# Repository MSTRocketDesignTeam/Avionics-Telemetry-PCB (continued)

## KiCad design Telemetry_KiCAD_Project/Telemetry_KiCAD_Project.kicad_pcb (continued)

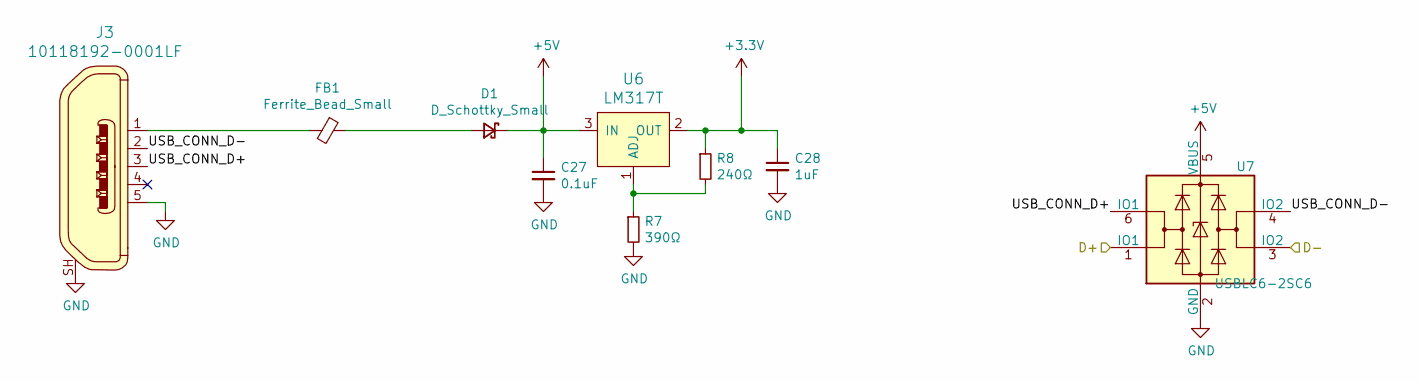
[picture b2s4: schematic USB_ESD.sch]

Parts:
C27: 0.1uF; C_0603_1608Metric
C28: 1uF; C_0603_1608Metric
D1: D_Schottky_Small; D_0201_0603Metric
FB1: Ferrite_Bead_Small; C_0603_1608Metric
J3: 10118192-0001LF; USB_Micro-B_Molex_47346-0001; MPN 10118192-0001LF; Digi-Key_PN 609-4613-1-ND
R7: 390Ω; 0603
R8: 240Ω; 0603
U6: LM317T; TO-252-3_TabPin2; MPN LM317T; Digi-Key_PN 497-1575-5-ND
U7: USBLC6-2SC6; SOT-23-6

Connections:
+3V3: C28.1, R8.1, U6.2 (OUT); also elsewhere on the board
+5V: C27.1, D1.1 (K), U6.3 (IN), U7.5 (VBUS); also elsewhere on the board
/USB Connector and ESD/D+: U7.1 (IO1); also elsewhere on the board
/USB Connector and ESD/D-: U7.3 (IO2); also elsewhere on the board
/USB Connector and ESD/USB_CONN_D+: J3.3, U7.6 (IO1)
/USB Connector and ESD/USB_CONN_D-: J3.2, U7.4 (IO2)
GND: C27.2, C28.2, J3.5, J3.SH, R7.2, U7.2 (GND); also elsewhere on the board
unnamed: D1.2 (A), FB1.1
unnamed: FB1.2, J3.1
unnamed: R7.1, R8.2, U6.1 (ADJ)

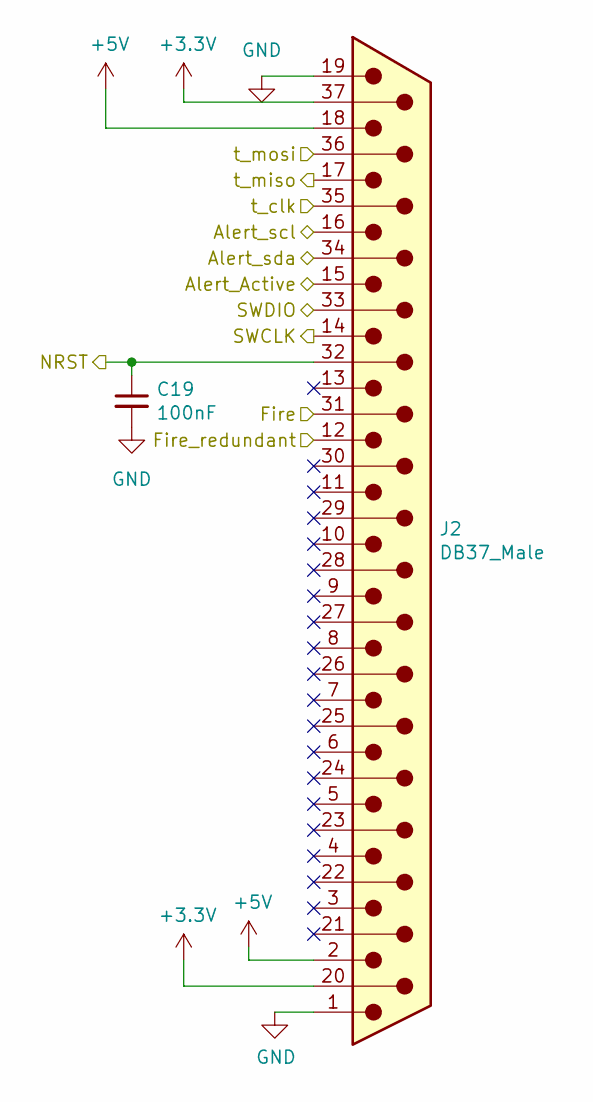
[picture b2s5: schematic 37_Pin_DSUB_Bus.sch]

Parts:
C19: 100nF; C_0603_1608Metric
J2: DB37_Male; DSUB-37_Male_Horizontal_P2.77x2.84mm_EdgePinOffset9.90mm_Ho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

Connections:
+3V3: J2.20, J2.37; also elsewhere on the board
+5V: J2.2, J2.18; also elsewhere on the board
/37_Pin_DSUB_Bus/Alert_Active: J2.15; also elsewhere on the board
/37_Pin_DSUB_Bus/Alert_scl: J2.16; also elsewhere on the board
/37_Pin_DSUB_Bus/Alert_sda: J2.34; also elsewhere on the board
/37_Pin_DSUB_Bus/NRST: C19.1, J2.32; also elsewhere on the board
/MCU_L562VE/ABORT_1: J2.31; also elsewhere on the board
/MCU_L562VE/ABORT_2: J2.12; also elsewhere on the board
/MCU_L562VE/DEBUG_SWCLK: J2.14; also elsewhere on the board
/MCU_L562VE/DEBUG_SWDIO: J2.33; also elsewhere on the board
/MCU_L562VE/SPI1_MISO: J2.17; also elsewhere on the board
/MCU_L562VE/SPI1_MOSI: J2.36; also elsewhere on the board
/MCU_L562VE/SPI1_SCK: J2.35; also elsewhere on the board
GND: C19.2, J2.1, J2.19; also elsewhere on the board

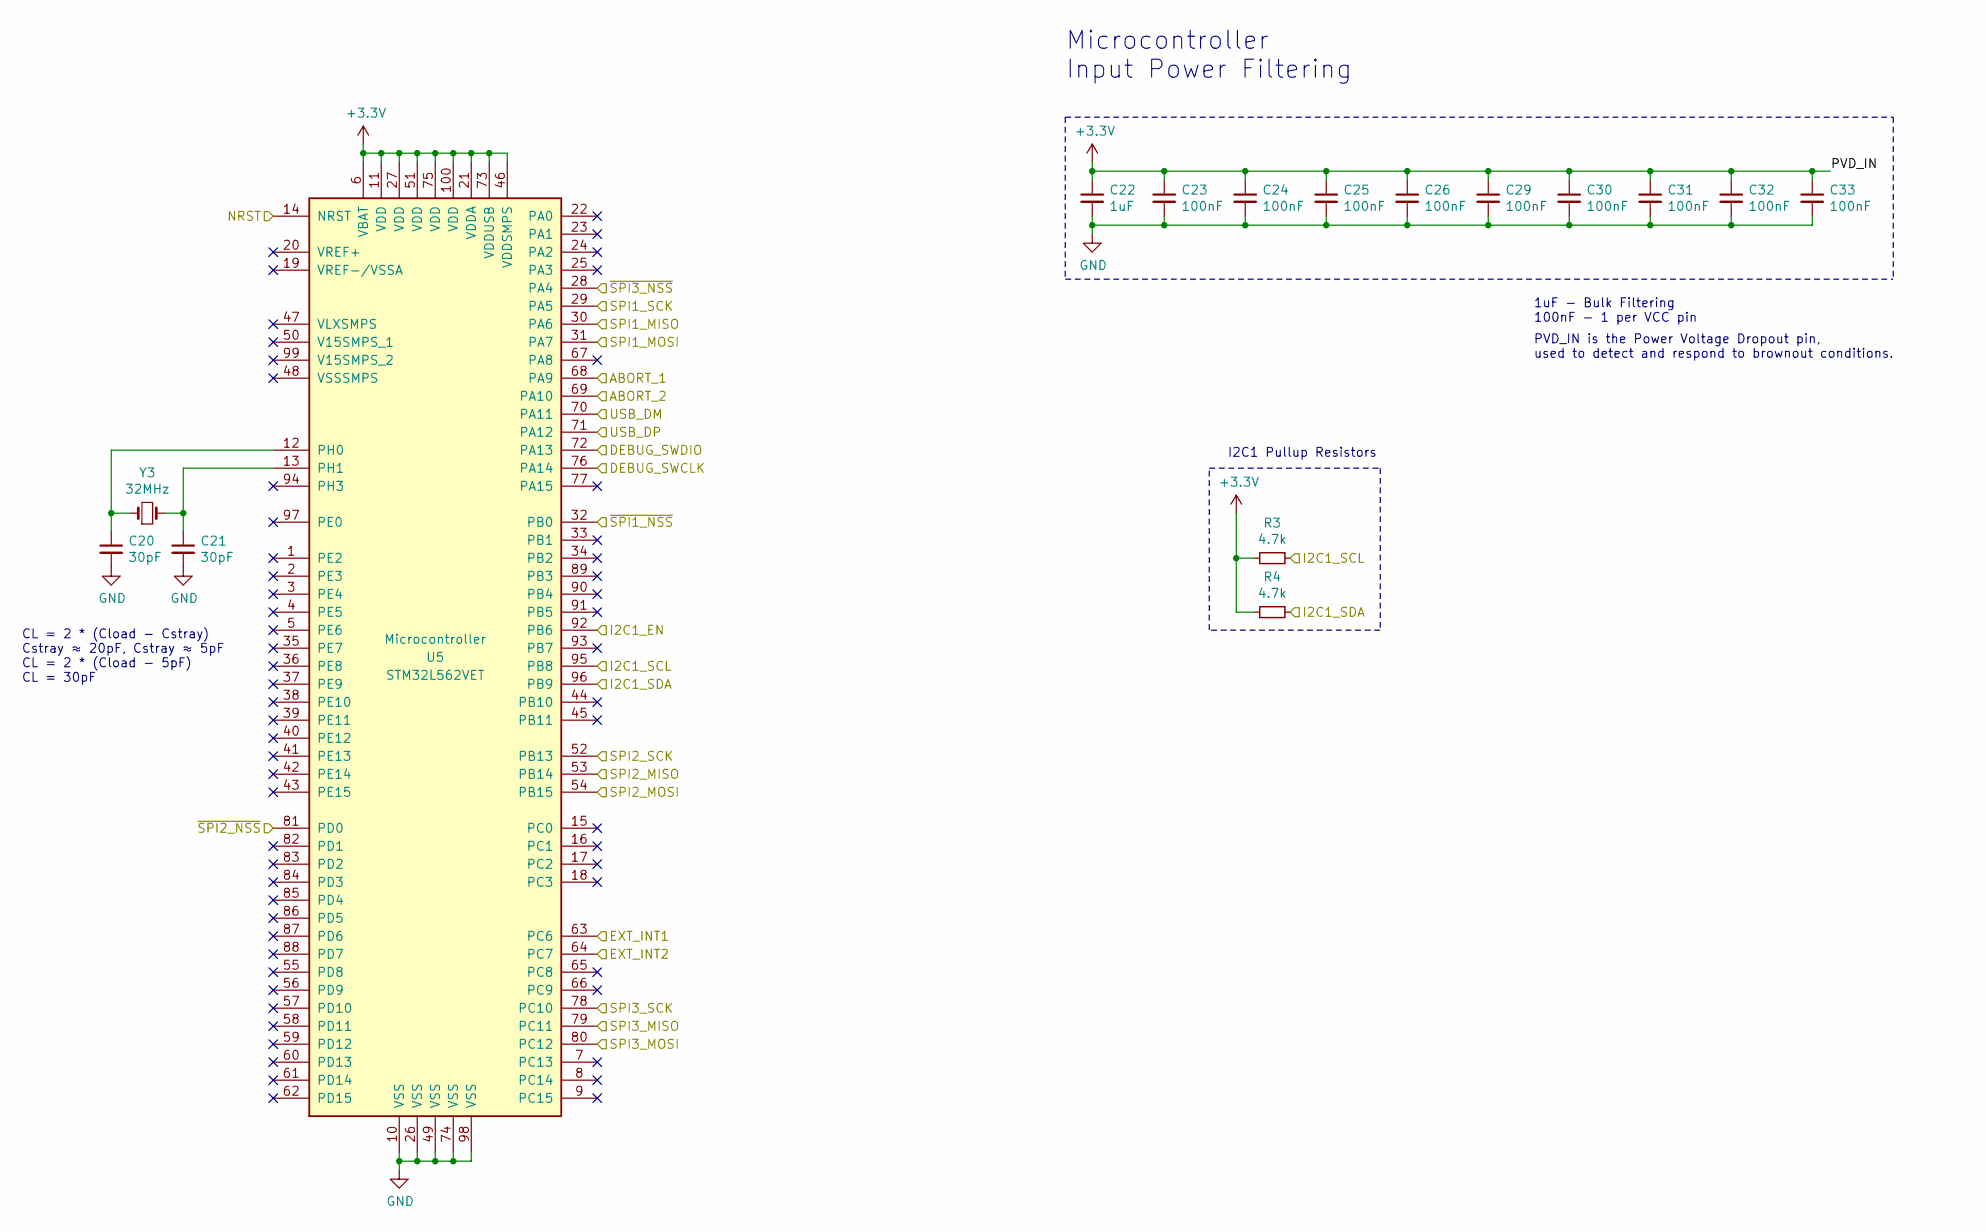
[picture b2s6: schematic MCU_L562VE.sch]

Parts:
C20, C21: 30pF; C_0603_1608Metric
C22: 1uF; C_0603_1608Metric
C23, C24, C25, C26, C29, C30, C31, C32, C33: 100nF; C_0603_1608Metric
R3, R4: 4.7k; 0603
U5: STM32L562VET; LQFP-100_14x14mm_P0.5mm
Y3: 32MHz; Crystal_SMD_0603-2Pin_6.0x3.5mm

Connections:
+3V3: C22.1, C23.1, C24.1, C25.1, C26.1, C29.1, C30.1, C31.1, C32.1, C33.1, R3.2, R4.2, U5.6 (VBAT), U5.11 (VDD), U5.21 (VDDA), U5.27 (VDD), U5.46 (VDDSMPS), U5.51 (VDD), U5.73 (VDDUSB), U5.75 (VDD), U5.100 (VDD); also elsewhere on the board
/37_Pin_DSUB_Bus/Alert_Active: U5.92 (PB6); also elsewhere on the board
/37_Pin_DSUB_Bus/Alert_scl: R3.1, U5.95 (PB8); also elsewhere on the board
/37_Pin_DSUB_Bus/Alert_sda: R4.1, U5.96 (PB9); also elsewhere on the board
/37_Pin_DSUB_Bus/NRST: U5.14 (NRST); also elsewhere on the board
/MCU_L562VE/ABORT_1: U5.68 (PA9); also elsewhere on the board
/MCU_L562VE/ABORT_2: U5.69 (PA10); also elsewhere on the board
/MCU_L562VE/DEBUG_SWCLK: U5.76 (PA14); also elsewhere on the board
/MCU_L562VE/DEBUG_SWDIO: U5.72 (PA13); also elsewhere on the board
/MCU_L562VE/SPI1_MISO: U5.30 (PA6); also elsewhere on the board
/MCU_L562VE/SPI1_MOSI: U5.31 (PA7); also elsewhere on the board
/MCU_L562VE/SPI1_SCK: U5.29 (PA5); also elsewhere on the board
/MCU_L562VE/~SPI1_NSS: U5.32 (PB0)
/RX_SCL: U5.78 (PC10); also elsewhere on the board
/RX_SDI: U5.80 (PC12); also elsewhere on the board
/RX_SDO: U5.79 (PC11); also elsewhere on the board
/TX_SCL: U5.52 (PB13); also elsewhere on the board
/TX_SDI: U5.54 (PB15); also elsewhere on the board
/TX_SDO: U5.53 (PB14); also elsewhere on the board
/USB Connector and ESD/D+: U5.71 (PA12); also elsewhere on the board
/USB Connector and ESD/D-: U5.70 (PA11); also elsewhere on the board
/~RX_IRQ: U5.64 (PC7); also elsewhere on the board
/~RX_SEL: U5.28 (PA4); also elsewhere on the board
/~TX_IRQ: U5.63 (PC6); also elsewhere on the board
/~TX_SEL: U5.81 (PD0); also elsewhere on the board
GND: C20.2, C21.2, C22.2, C23.2, C24.2, C25.2, C26.2, C29.2, C30.2, C31.2, C32.2, C33.2, U5.10 (VSS), U5.26 (VSS), U5.49 (VSS), U5.74 (VSS), U5.98 (VSS); also elsewhere on the board
unnamed: C20.1, U5.12 (PH0), Y3.1
unnamed: C21.1, U5.13 (PH1), Y3.2

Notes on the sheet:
Microcontroller Input Power Filtering
1uF - Bulk Filtering 100nF - 1 per VCC pin
PVD_IN is the Power Voltage Dropout pin, used to detect and respond to brownout conditions.
I2C1 Pullup Resistors
CL = 2 * (Cload - Cstray) Cstray ≈ 20pF, Cstray ≈ 5pF CL = 2 * (Cload - 5pF) CL = 30pF

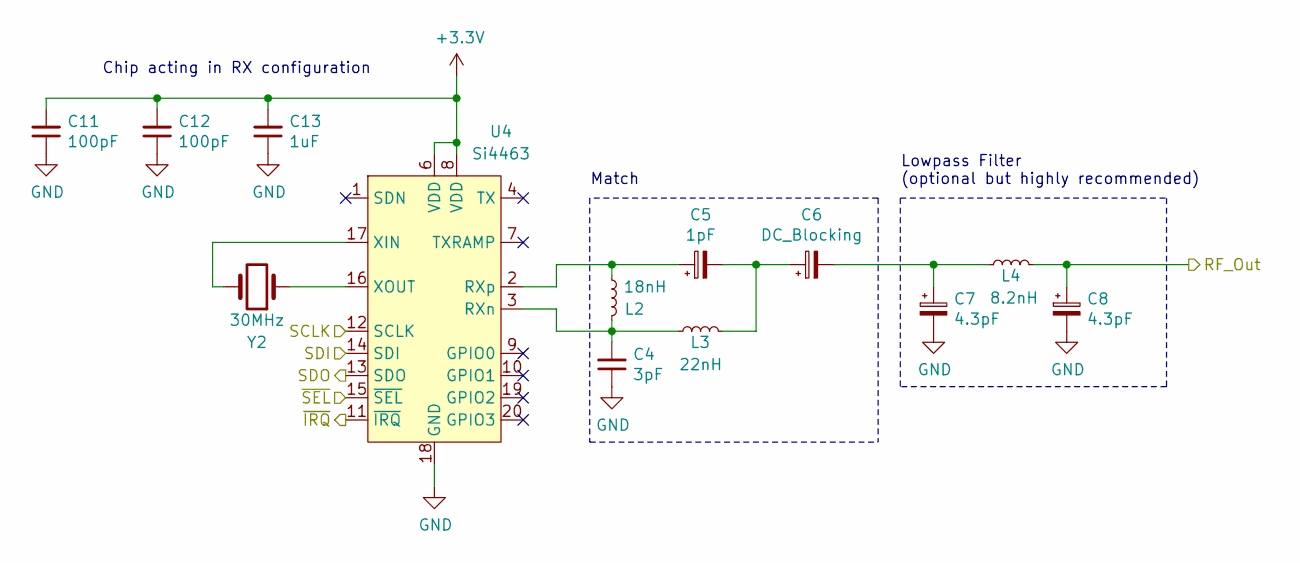
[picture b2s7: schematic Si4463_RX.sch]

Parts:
C1, C2: 100pF; C_0603_1608Metric
C3: 1uF; C_0603_1608Metric
C4: 3pF; C_0603_1608Metric
C5: 1pF; C_0603_1608Metric
C6: DC_Blocking; C_0603_1608Metric
C7, C8: 4.3pF; C_0603_1608Metric
L2: 18nH; L_0603_1608Metric
L3: 22nH; L_0603_1608Metric
L4: 8.2nH; L_0603_1608Metric
U2: Si4463; QFN-20-1EP_4x4mm_P0.5mm_EP2.6x2.6mm_ThermalVias
Y1: 30MHz; Crystal_SMD_0603-2Pin_6.0x3.5mm

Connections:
+3V3: C1.2, C2.2, C3.2, U2.6 (VDD), U2.8 (VDD); also elsewhere on the board
/RX_Si4463/RF_Out: C8.1, L4.2; also elsewhere on the board
/TX_SCL: U2.12 (SCLK); also elsewhere on the board
/TX_SDI: U2.14 (SDI); also elsewhere on the board
/TX_SDO: U2.13 (SDO); also elsewhere on the board
/~TX_IRQ: U2.11 (~IRQ); also elsewhere on the board
/~TX_SEL: U2.15 (~SEL); also elsewhere on the board
GND: C1.1, C2.1, C3.1, C4.1, C7.2, C8.2, U2.18 (GND), U2.21 (GND); also elsewhere on the board
unnamed: C5.2, C6.1, L3.2
unnamed: C6.2, C7.1, L4.1
unnamed 35: U2.4 (TX); also elsewhere on the board
unnamed: U2.16 (XOUT), Y1.1
unnamed: U2.17 (XIN), Y1.2

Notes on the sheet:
Chip acting in RX configuration
Lowpass Filter (optional but highly recommended)
Match

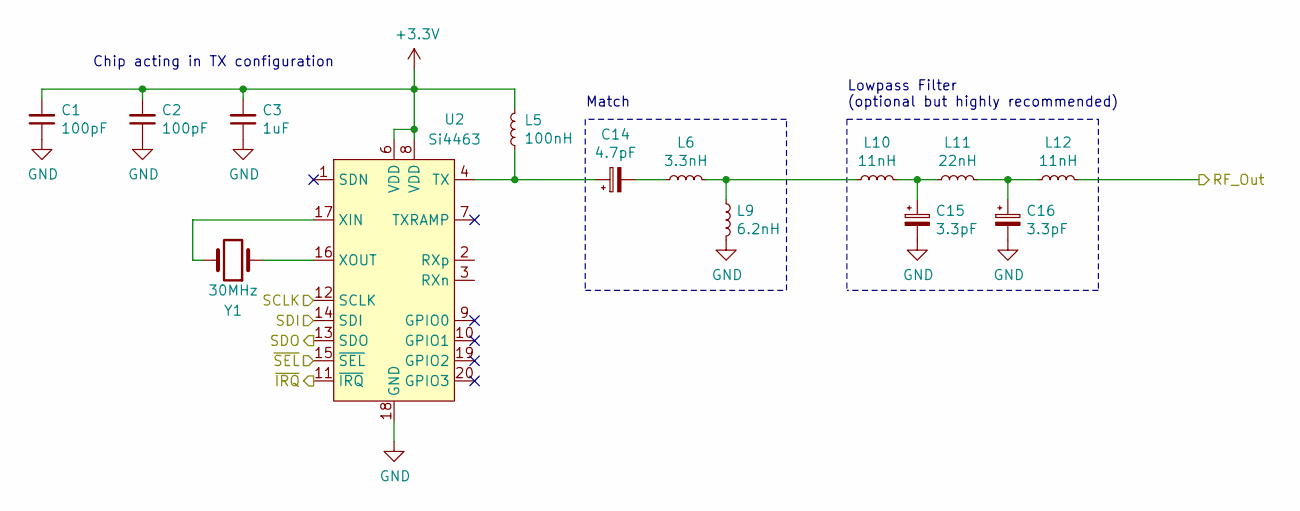
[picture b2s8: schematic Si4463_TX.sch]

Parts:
C1, C2: 100pF; C_0603_1608Metric
C3: 1uF; C_0603_1608Metric
C14: 4.7pF; C_0603_1608Metric
C15, C16: 3.3pF; C_0603_1608Metric
L5: 100nH; L_0603_1608Metric
L6: 3.3nH; L_0603_1608Metric
L9: 6.2nH; L_0603_1608Metric
L10, L12: 11nH; L_0603_1608Metric
L11: 22nH; L_0603_1608Metric
U2: Si4463; QFN-20-1EP_4x4mm_P0.5mm_EP2.6x2.6mm_ThermalVias
Y1: 30MHz; Crystal_SMD_0603-2Pin_6.0x3.5mm

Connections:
+3V3: C1.2, C2.2, C3.2, L5.2, U2.6 (VDD), U2.8 (VDD); also elsewhere on the board
/ADL_Amplifier/RF_In: L12.2; also elsewhere on the board
/TX_SCL: U2.12 (SCLK); also elsewhere on the board
/TX_SDI: U2.14 (SDI); also elsewhere on the board
/TX_SDO: U2.13 (SDO); also elsewhere on the board
/~TX_IRQ: U2.11 (~IRQ); also elsewhere on the board
/~TX_SEL: U2.15 (~SEL); also elsewhere on the board
GND: C1.1, C2.1, C3.1, C15.2, C16.2, L9.2, U2.18 (GND), U2.21 (GND); also elsewhere on the board
unnamed: C14.1, L5.1, U2.4 (TX)
unnamed: C14.2, L6.1
unnamed: C15.1, L10.2, L11.1
unnamed: C16.1, L11.2, L12.1
unnamed: L6.2, L9.1, L10.1
unnamed: U2.16 (XOUT), Y1.1
unnamed: U2.17 (XIN), Y1.2

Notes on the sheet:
Chip acting in TX configuration
Lowpass Filter (optional but highly recommended)
Match

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
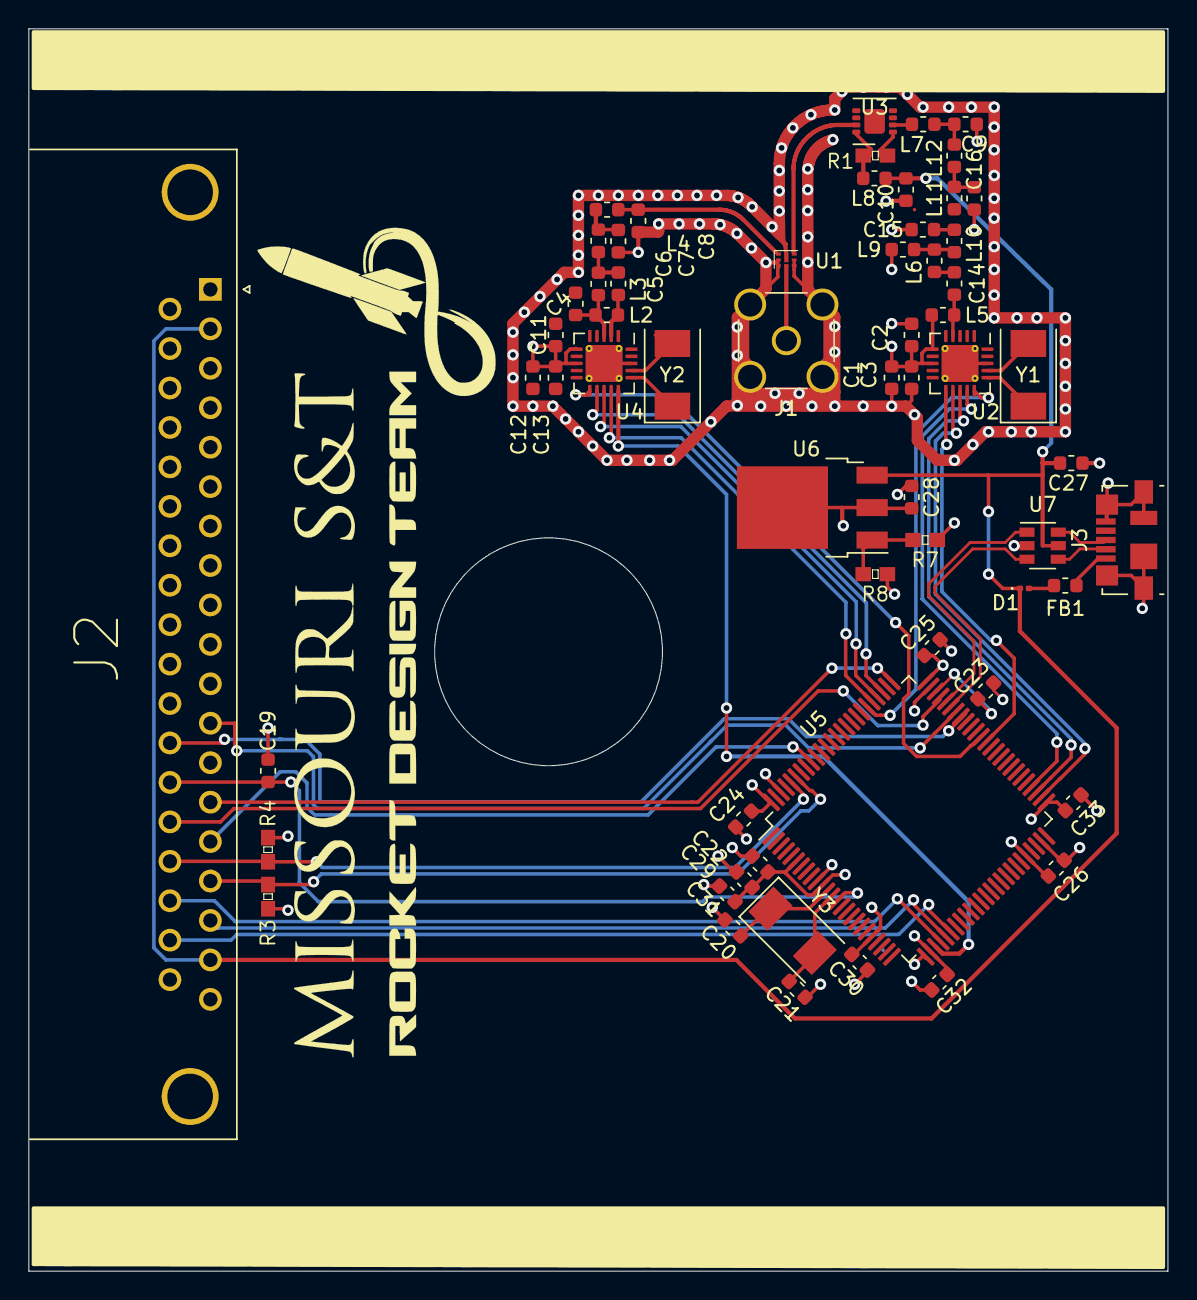
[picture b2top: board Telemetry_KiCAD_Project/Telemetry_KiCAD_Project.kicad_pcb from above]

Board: 4 copper layers, 80.0 x 87.3 mm, 62 parts (0 on the bottom side), 53 nets.

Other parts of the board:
C11, C12: 100pF; C_0603_1608Metric
C13: 1uF; C_0603_1608Metric
U4: Si4463; QFN-20-1EP_4x4mm_P0.5mm_EP2.6x2.6mm_ThermalVias
Y2: 30MHz; Crystal_SMD_0603-2Pin_6.0x3.5mm

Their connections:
+3V3: C11.2, C12.2, C13.2, U4.6, U4.8; also elsewhere on the board
/RX_SCL: U4.12; also elsewhere on the board
/RX_SDI: U4.14; also elsewhere on the board
/RX_SDO: U4.13; also elsewhere on the board
/~RX_IRQ: U4.11; also elsewhere on the board
/~RX_SEL: U4.15; also elsewhere on the board
GND: C11.1, C12.1, C13.1, U4.18, U4.21; also elsewhere on the board
unnamed: U4.16, Y2.1
unnamed: U4.17, Y2.2

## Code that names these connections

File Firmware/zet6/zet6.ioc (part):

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Mcu.Name=STM32L562ZETx
Mcu.Package=LQFP144
Mcu.UserName=STM32L562ZETx
PA11.Mode=Device
PA11.Signal=USB_DM
PA12.Mode=Device
PA12.Signal=USB_DP
PB13.Mode=Full_Duplex_Master
PB13.Signal=SPI2_SCK
PB14.Mode=Full_Duplex_Master
PB14.Signal=SPI2_MISO
PB15.Mode=Full_Duplex_Master
PB15.Signal=SPI2_MOSI
PC10.Mode=Full_Duplex_Master
PC10.Signal=SPI3_SCK
PC11.Mode=Full_Duplex_Master
PC11.Signal=SPI3_MISO
PC12.Mode=Full_Duplex_Master
PC12.Signal=SPI3_MOSI
PD0.GPIOParameters=PinState
PD0.PinState=GPIO_PIN_SET
PD0.Signal=GPIO_Output
PD8.Signal=GPIO_Output
PE10.GPIOParameters=PinState
PE10.PinState=GPIO_PIN_RESET
PE10.Signal=GPIO_Output
PE11.GPIOParameters=PinState
PE11.PinState=GPIO_PIN_RESET
PE11.Signal=GPIO_Output
PE7.GPIOParameters=PinState
PE7.PinState=GPIO_PIN_RESET
PE7.Signal=GPIO_Output
PE8.GPIOParameters=PinState
PE8.PinState=GPIO_PIN_RESET
PE8.Signal=GPIO_Output
PE9.GPIOParameters=PinState
PE9.PinState=GPIO_PIN_RESET
PE9.Signal=GPIO_Output
PH0-OSC_IN\ (PH0).Mode=HSE-External-Oscillator
PH0-OSC_IN\ (PH0).Signal=RCC_OSC_IN
PH1-OSC_OUT\ (PH1).Mode=HSE-External-Oscillator
PH1-OSC_OUT\ (PH1).Signal=RCC_OSC_OUT
RCC.HSE_VALUE=32000000
RCC.SYSCLKFreq_VALUE=110000000
RCC.SYSCLKSource=RCC_SYSCLKSOURCE_PLLCLK
board=custom

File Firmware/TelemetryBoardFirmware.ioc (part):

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Mcu.Name=STM32L562VETxQ
Mcu.Package=LQFP100
Mcu.UserName=STM32L562VETxQ
PA1.Mode=Full_Duplex_Master
PA1.Signal=SPI1_SCK
PA11.Mode=Device
PA11.Signal=USB_DM
PA12.Mode=Device
PA12.Signal=USB_DP
PA13\ (JTMS/SWDIO).Mode=Trace_Asynchronous_SW
PA13\ (JTMS/SWDIO).Signal=DEBUG_JTMS-SWDIO
PA14\ (JTCK/SWCLK).Mode=Trace_Asynchronous_SW
PA14\ (JTCK/SWCLK).Signal=DEBUG_JTCK-SWCLK
PA6.Mode=Full_Duplex_Master
PA6.Signal=SPI1_MISO
PA7.Mode=Full_Duplex_Master
PA7.Signal=SPI1_MOSI
PB10.Mode=Full_Duplex_Master
PB10.Signal=SPI2_SCK
PB3\ (JTDO/TRACESWO).Mode=Trace_Asynchronous_SW
PB3\ (JTDO/TRACESWO).Signal=DEBUG_JTDO-SWO
PB6.Mode=I2C
PB6.Signal=I2C1_SCL
PB7.Mode=I2C
PB7.Signal=I2C1_SDA
PC1.Mode=Full_Duplex_Master
PC1.Signal=SPI2_MOSI
PC10.Mode=Full_Duplex_Master
PC10.Signal=SPI3_SCK
PC11.Mode=Full_Duplex_Master
PC11.Signal=SPI3_MISO
PC12.Mode=Full_Duplex_Master
PC12.Signal=SPI3_MOSI
PC14-OSC32_IN\ (PC14).Mode=LSE-External-Clock-Source
PC14-OSC32_IN\ (PC14).Signal=RCC_OSC32_IN
PC2.Mode=Full_Duplex_Master
PC2.Signal=SPI2_MISO
PH0-OSC_IN\ (PH0).Mode=HSE-External-Oscillator
PH0-OSC_IN\ (PH0).Signal=RCC_OSC_IN
PH1-OSC_OUT\ (PH1).Mode=HSE-External-Oscillator
PH1-OSC_OUT\ (PH1).Signal=RCC_OSC_OUT
RCC.HSE_VALUE=32000000
board=custom

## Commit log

2021-08-05 Created initial README file for the scope of the project
    This is also a test of the git and branch merging.
2021-08-05 PCB dimensions now all in mm
2021-08-05 Included KiCad STM32 pcb tutorial youtube link
2021-09-30 Create LICENSE
2021-10-02 Schematic v1.0.0
    Creation of KiCAD project file, initial draft of PCB schematic file, components chosen as a starting point and will likely be altered in future revisions.
2021-10-02 Schematic v1.0.1
    Corrected page settings.
2021-11-24 Included Amplifier, New Transceivers, Duplexer, and 37 Pin DSUB
    Still want to replace the microcontroller, will happen in next commit
2021-11-25 Replaced L151CBT with L552CC
    This is the same MCU as in the Data Collection board, should simplify testing and part ordering.
    A custom symbol was made and added to the RDT_Custom_Symbols library.
2021-11-25 Renamed Coax Connector Symbol
2021-11-25 Added USB ESD, relocated Debug pins
2021-11-25 Correct SPI bus lines on main page
2021-11-25 Added chip select functions for RX and TX chips
    The Si4463 datasheet mentions that some parameters can be quickly accessed if the chip select line is toggled
2021-11-25 Small clean up for MCU page
2021-11-25 Annotated Components
2021-11-25 I2C2 removed from MCU
    Carry over from copying the file from the Data Collection board
2021-11-25 Corrected hierarchical pin directions, squashed bugs
    There are still some warnings about pins being connected but not driven, don't know how to fix those at the moment
2021-11-25 Assigned footprints to all components (except duplexer)
2021-11-25 Created initial ratsnest
2021-11-26 Added STM32L562VET Symbol
2021-11-29 Replaced STM32L552 with STM32L562
    Now in a QFPN-100 package, lot's o' pins!
2021-11-30 Assigned capacitors for new MCU
2021-12-01 Initial PCB dimensions and production settings
2021-12-01 Placed DB37 connector
    Might require some alignment later
2021-12-01 PCB Layout Progress
2021-12-03 Created separate schematics for chips acting in TX and RX
    Added link to document describing passive component selection
2021-12-03 Added TX/RX matching network passives to PCB
2021-12-04 Added RSD Duplexer Footprint, rearranged RF matching networks
2021-12-04 PCB Layout Progress
    Everything appears to be connected...
2021-12-04 Added RF trace clearances
2021-12-04 Added via fences to RF section, adjusted labels
2021-12-04 Added RDT logo and edge graphics
2021-12-04 Changed USB connector to Molex
2021-12-04 Fixed unconnected ground pin on duplexer chip
2021-12-04 Fixed more unconnected ground pads
2021-12-06 Majorly Reorganized Project Directory
    This is done in an effort to help keep the repo organized and modularized.
2021-12-06 Squashed commit of the following:
    commit dd5425a15ec90373b5e960bf340bab0c3bd07ece
    Merge: 8a575c8 cd97259
    Author: Thomas Francois <twfth9@mst.edu>
    Date: Sun Dec 5 21:38:26 2021 -0600
    Merge branch 'master' of https://github.com/MSTRocketDesignTeam/Avionics-Telemetry-PCB
    commit 8a575c872352ae5a3f01950cdc10612db62a8baa
2021-12-06 Backlink to CADLAB.io has been added.
2021-12-06 Added test points to main schematic page
    Also corrected library table
2021-12-06 Added and connected test points
2021-12-06 Fixed merge mistakes between branches
2021-12-19 Added SPI debug connectors to SPI busses
2021-12-19 Arranged TX and RX chip matching networks
2021-12-19 Adjustments to RF chip placements
2021-12-19 Placed RF traces w/rounded corners
2021-12-19 Added USB components
2021-12-19 Added more USB components
2021-12-19 Updated DSUB connector assignments
    Welp, looks like everything got turned upside down, time to flip everything on the board, ugh
2021-12-19 Oriented MCU
2021-12-20 Arranged TX and RX SPI busses
    It just occurred to me that I could just swap the TX and RX SPI busses and routing would be 1000% easier. D'oh!
2021-12-20 Swapped SPI2 and SPI3 for TX/RX chips
2021-12-20 Routed TX Chip SPI bus
2021-12-20 Routed RX Chip SPI bus
2021-12-20 Routed DB37 connector
2021-12-20 Routed debug connectors
2021-12-20 Reworked RX SPI lines
2021-12-20 Routed RF traces
2021-12-20 Added via fences to RF traces
2021-12-20 Placed decoupling capacitors for MCU
2021-12-20 Improved via fence around sma connector
2021-12-20 Tidied up remaining ratsnest lines
    Version 2 complete
2021-12-20 Adjusted component silk screen, added pcb extensions
2021-12-20 Tweaked via fence connection to duplexer
2021-12-20 Connected C18 to L5
2021-12-20 Added copper pours, removed filled zones around RF section
2022-01-17 Major Redesign
    - Copper ground pours on F and B.
    - Improved isolation between data lines
    - Expanded via fences around RF section.
    - GND plane isolation peninsulas for crystals.
    - Simplified I2C, SPI, and USB lines for reduced interference.
    - Added 3D models for all components.
2022-01-17 Fixed some unconnected GND stitching vias
2022-01-17 Connected some unconnected GND stitching vias
2022-01-17 Corrected TX/RX crystal grounds
2022-01-17 Added 3D models for TX/RX chips
2022-01-17 Added 3D model for ADL5521
2022-01-17 Refined via fences
2022-01-17 Rounded PCB edges
2022-01-18 Updated PCB edge silkscreen and rounded edge cuts corner on DSUB side
2022-01-18 added qr code
    qr code was added to the board on the back silkscreen
2022-01-18 Adjusted position of USB connector and components, length matched data lines
2022-01-18 Added status LEDs for MCU
2022-01-18 Added silk screen art
2022-01-19 Initial commit for VET6Q chip software with IDE project
2022-01-19 spelling
2022-01-19 Updated crystal footprints, added 3D model
    PCB layout now invalid, changes pending
2022-01-19 Added larger crystals to TX/RX and MCU chips
2022-01-19 Added reset button to NRST line
2022-01-19 Added header pins for PH3 bootloader toggling
2022-01-19 Connected unconnected MCU filter caps
2022-01-19 Documentation update and project settings update
2022-01-19 Readded 3D models for crystals
2022-01-19 Corrected jumper on MCU sheet
2022-01-19 Corrected center pin of RSD chip footprint
2022-01-19 Git oopsie
2022-01-19 Added JLCPCB component tags
2022-01-21 added csv files
2022-01-21 Update item tags
2022-01-21 Updated CPL Headers
2022-01-21 Added WHF logo to pcb
2022-01-21 Updated gitignore
2022-01-21 Adapted layout to different linear regulator for USB
2022-01-23 updated gerbers
2022-01-24 Organized repo
2022-01-25 Added signatures to silkscreen
2022-01-27 Updated production files
2022-01-28 updated software toolchain and added binaries
2022-02-23 Updated SMPS wiring and voltage regulator footprint
2022-02-24 no message
2022-02-24 Grounded VSSA
2022-02-24 Added capacitor between VDDA and VSSA
2022-02-25 Adjusted some trace thicknesses, added more vias to USB voltage regulator
2022-02-28 Corrected microcontroller component sheet
2022-02-28 Adjusted edge cuts, aligned silkscreen, center hole, all components
    Some traces still need to be adjusted, i.e. status LEDs
2022-02-28 Adjusted board dimension labels
2022-02-28 Corrected edge cuts
2022-03-01 Changed 3D models to .step
2022-03-01 Added pullup resistor for boot pin
2022-03-02 Increased spacing around MCU, added filter caps for SMPS, rerouted 5V from DSUB, changed SMA to right angle
2022-03-02 Added male sma model to coax connector for assisting in alignment
2022-03-07 Adjusted silkscreen
2022-03-07 Added more silkscreen art
2022-03-23 Adjusted 5V lines, corrected ground fences, added cutout for USB connector
2022-03-23 Adjusted keepout area around MCU crystal
2022-03-24 Regenerated production files and updated sheet labels
2022-03-24 Updated schematic labels, Version 2.0.0
2022-03-26 Changed D1 LCSC to make component fit on pads
2022-05-08 syncing files
2022-05-08 Restructured Firmware
2022-05-08 redid firmware
2022-08-19 Added more JLC part numbers and added missing voltage regulator connection
2022-08-19 edited routing, added more jlc part numbers, organized files, and regenerated production files
2022-08-19 removed autosave files
2022-08-21 Updated LCSC numbers and production files
2022-08-27 Added resistor that was missing, connected a resistor that was floating, and updated LCSC numbers
2022-08-27 Fixed incorrect LCSC numbers
2022-11-06 Updated DSUB model and generated STEP model of board
2022-11-10 Initial import of STM32L562ZET6
2022-11-10 Schematic complete with STM32L562ZET6
2022-11-10 started changing chip on-board
2022-11-10 fixed board update issue by renaming usb pin 0 and DSUB pin 0
2022-11-10 Initial routing pass
2022-11-11 fixed weird routing
2022-11-12 tried to minimize loops and traces under the IC
2022-11-12 more fine tuning
2022-11-17 Updated LCSC and production files
2022-11-27 Cleaned up RF signal path
2022-11-28 Rerouted some stuffs, close to final for Rev 3
2022-12-11 Moved voltage regulator down to make room for the case
2022-12-11 Moved voltage regulator down to make room for the case and cleaned up some routing
2022-12-11 Fixed git errors
2022-12-11 Adjusted RF fences, tuned USB trace lengths, adjusted GND pours
2022-12-11 Added step file for the case
2022-12-11 Updated production files for V3
2022-12-11 Split the case step file into the lid and case
2022-12-12 Updated LCSC numbers and cleaned up routing
2022-12-14 Updated USB connector part number based on manufacturer feedback
2022-12-14 Corrected USB footprint and moved USB edge cut
2022-12-14 Added 3D models to USB and MCU, adjusted C31 label
2022-12-31 Changed SPI debug headers to be a proper header component. Updated 3D model
2022-12-31 switched voltage regulator resistors
2022-12-31 updated routing and silkscreen
2023-01-02 reset capacitor routing from underneath switch
2023-01-03 Updated LCSC numbers, updated BOM file, added power LED.
2023-01-04 Regenerated gerbers, refilled zones, and wrote firmware that causes leds to blink in sequence.
2023-01-04 configured SPI2, SPI3, and USB
2023-01-07 Updated SPI pins. Added onboard JTAG header
2023-01-07 Routed JTAG connector and set boot0 default to GND
2023-01-07 routing and changed to rev 4
2023-01-08 Added LCSC Number to JTAG connector
